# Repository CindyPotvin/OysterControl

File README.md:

# Oyster Control Arduino shield

An Arduino shield to control 3 5V devices over USB, and a 24V devices (an humidifier) to grow oyster mushrooms in a box. Includes the Kicad project with the schematic and PCB, and the Arduino sketch.

See the blog post
https://robotsbench.com/custom-arduino-uno-shield-for-growing-oyster-mushrooms/ for more details about building the shield.

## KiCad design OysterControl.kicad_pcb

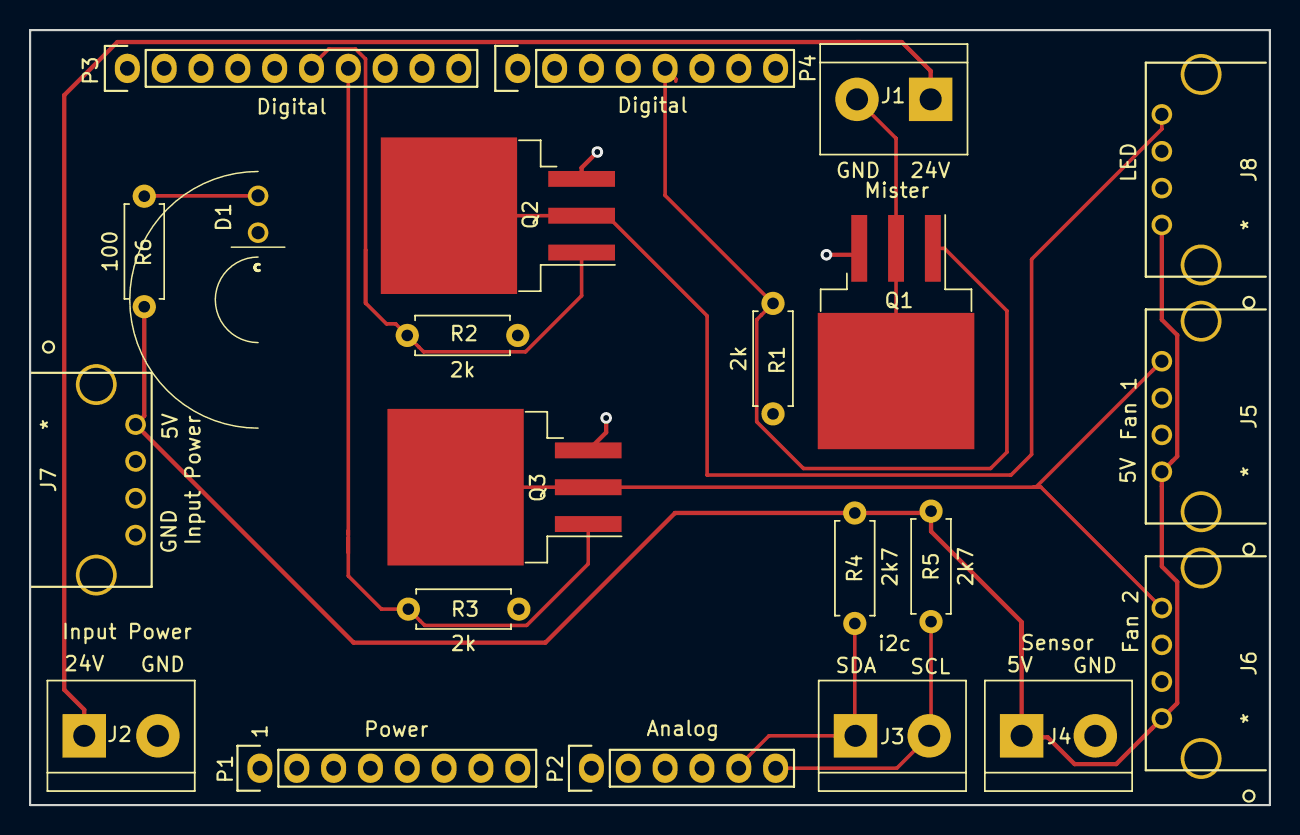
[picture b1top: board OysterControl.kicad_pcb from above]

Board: 2 copper layers, 85.5 x 53.4 mm, 22 parts (0 on the bottom side), 12 nets.

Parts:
D1: LED; LTL2R3KGDEM
J1: Mister; TerminalBlock_bornier-2_P5.08mm
J2: Input Power; TerminalBlock_bornier-2_P5.08mm
J3: i2c; TerminalBlock_bornier-2_P5.08mm
J4: Sensor; TerminalBlock_bornier-2_P5.08mm
J5: Fan 1; SS-52100-001
J6: Fan 2; SS-52100-001
J7: Input Power; SS-52100-001
J8: LED; SS-52100-001
P1: Power; Socket_Strip_Arduino_1x08
P2: Analog; Socket_Strip_Arduino_1x06
P3: Digital; Socket_Strip_Arduino_1x10
P4: Digital; Socket_Strip_Arduino_1x08
Q1, Q2, Q3: IRF520NSTRLPBF; TO-263-3_TabPin2
R1, R2, R3: 2k; R_Axial_DIN0207_L6.3mm_D2.5mm_P7.62mm_Horizontal
R4, R5: 2k7; R_Axial_DIN0207_L6.3mm_D2.5mm_P7.62mm_Horizontal
R6: 100; R_Axial_DIN0207_L6.3mm_D2.5mm_P7.62mm_Horizontal

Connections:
/3(MIST): P4.5, Q1.1, R1.1
/11(FAN): P3.7, Q3.1, R3.1
/12(LED): P3.6, Q2.1, R2.1
/+5V: J4.1, J5.1, J6.1, J7.1, J8.1, R4.1, R5.1, R6.2
/+24V: J1.1, J2.1
/A4(SDA): J3.1, P2.5, R4.2
/A5(SCL): J3.2, P2.6, R5.2
GND: D1.1, J2.2, J4.2, J7.4, P1.6, P1.7, P3.4, Q1.3, Q2.3, Q3.3, R1.2, R2.2, R3.2
unnamed: D1.2, R6.1
unnamed: J1.2, Q1.2
unnamed: J5.4, J6.4, Q3.2
unnamed: J8.4, Q2.2

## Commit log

2022-02-04 Arduino sketch
2022-02-04 Update README.md
    Add more details about the content of the project.

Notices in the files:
parts and their libraries:
Copyright 2016 Accelerated Designs. All rights reserved.
